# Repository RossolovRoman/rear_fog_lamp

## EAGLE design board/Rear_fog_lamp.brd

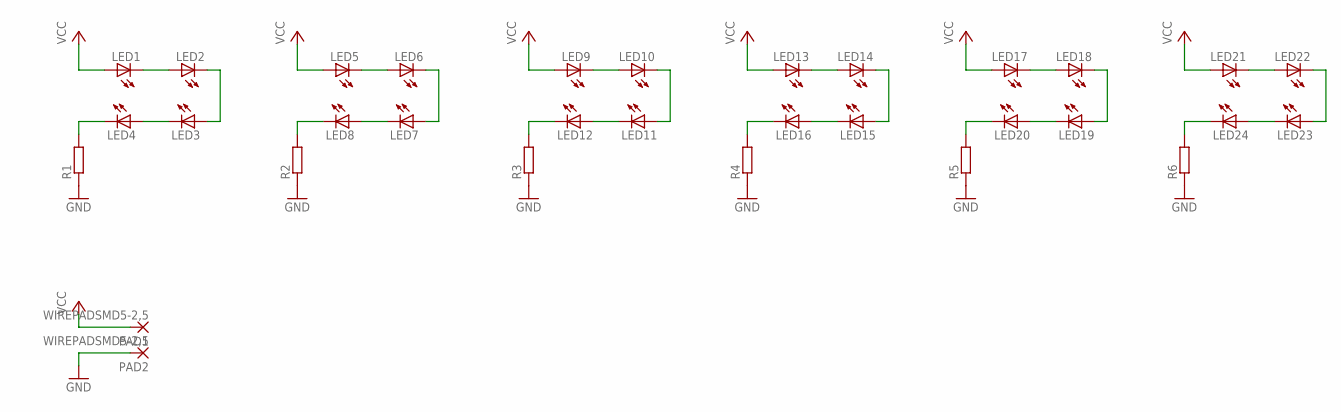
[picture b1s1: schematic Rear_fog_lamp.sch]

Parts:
LED1, LED2, LED3, LED4, LED5, LED6, LED7, LED8, LED9, LED10, LED11, LED12, LED13, LED14, LED15, LED16, LED17, LED18, LED19, LED20, LED21, LED22, LED23, LED24: LED5MM
PAD1, PAD2: WIREPADSMD5-2,5; 5-2,5
R1, R2, R3, R4, R5, R6: R-EU_0204/7; 0204/7

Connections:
GND: PAD2.1, R1.1, R2.1, R3.1, R4.1, R5.1, R6.1
unnamed: LED1.K (C), LED2.A
unnamed: LED2.K (C), LED3.A
unnamed: LED3.K (C), LED4.A
unnamed: LED4.K (C), R1.2
unnamed: LED5.K (C), LED6.A
unnamed: LED6.K (C), LED7.A
unnamed: LED7.K (C), LED8.A
unnamed: LED8.K (C), R2.2
unnamed: LED9.K (C), LED10.A
unnamed: LED10.K (C), LED11.A
unnamed: LED11.K (C), LED12.A
unnamed: LED12.K (C), R3.2
unnamed: LED13.K (C), LED14.A
unnamed: LED14.K (C), LED15.A
unnamed: LED15.K (C), LED16.A
unnamed: LED16.K (C), R4.2
unnamed: LED17.K (C), LED18.A
unnamed: LED18.K (C), LED19.A
unnamed: LED19.K (C), LED20.A
unnamed: LED20.K (C), R5.2
unnamed: LED21.K (C), LED22.A
unnamed: LED22.K (C), LED23.A
unnamed: LED23.K (C), LED24.A
unnamed: LED24.K (C), R6.2
VCC: LED1.A, LED5.A, LED9.A, LED13.A, LED17.A, LED21.A, PAD1.1

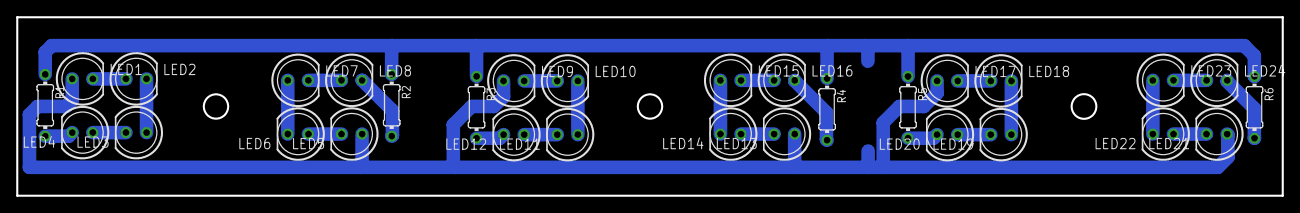
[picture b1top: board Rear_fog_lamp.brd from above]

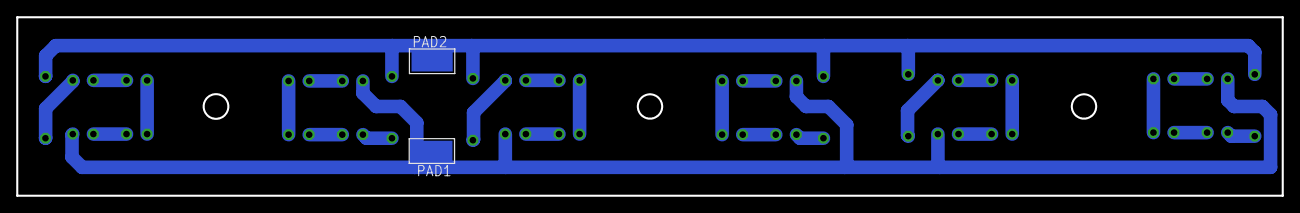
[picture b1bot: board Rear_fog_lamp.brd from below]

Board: 2 copper layers, 156.0 x 22.0 mm, 32 parts (2 on the bottom side), 26 nets.

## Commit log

2019-07-20 Добавлены эл. схема и плата.
